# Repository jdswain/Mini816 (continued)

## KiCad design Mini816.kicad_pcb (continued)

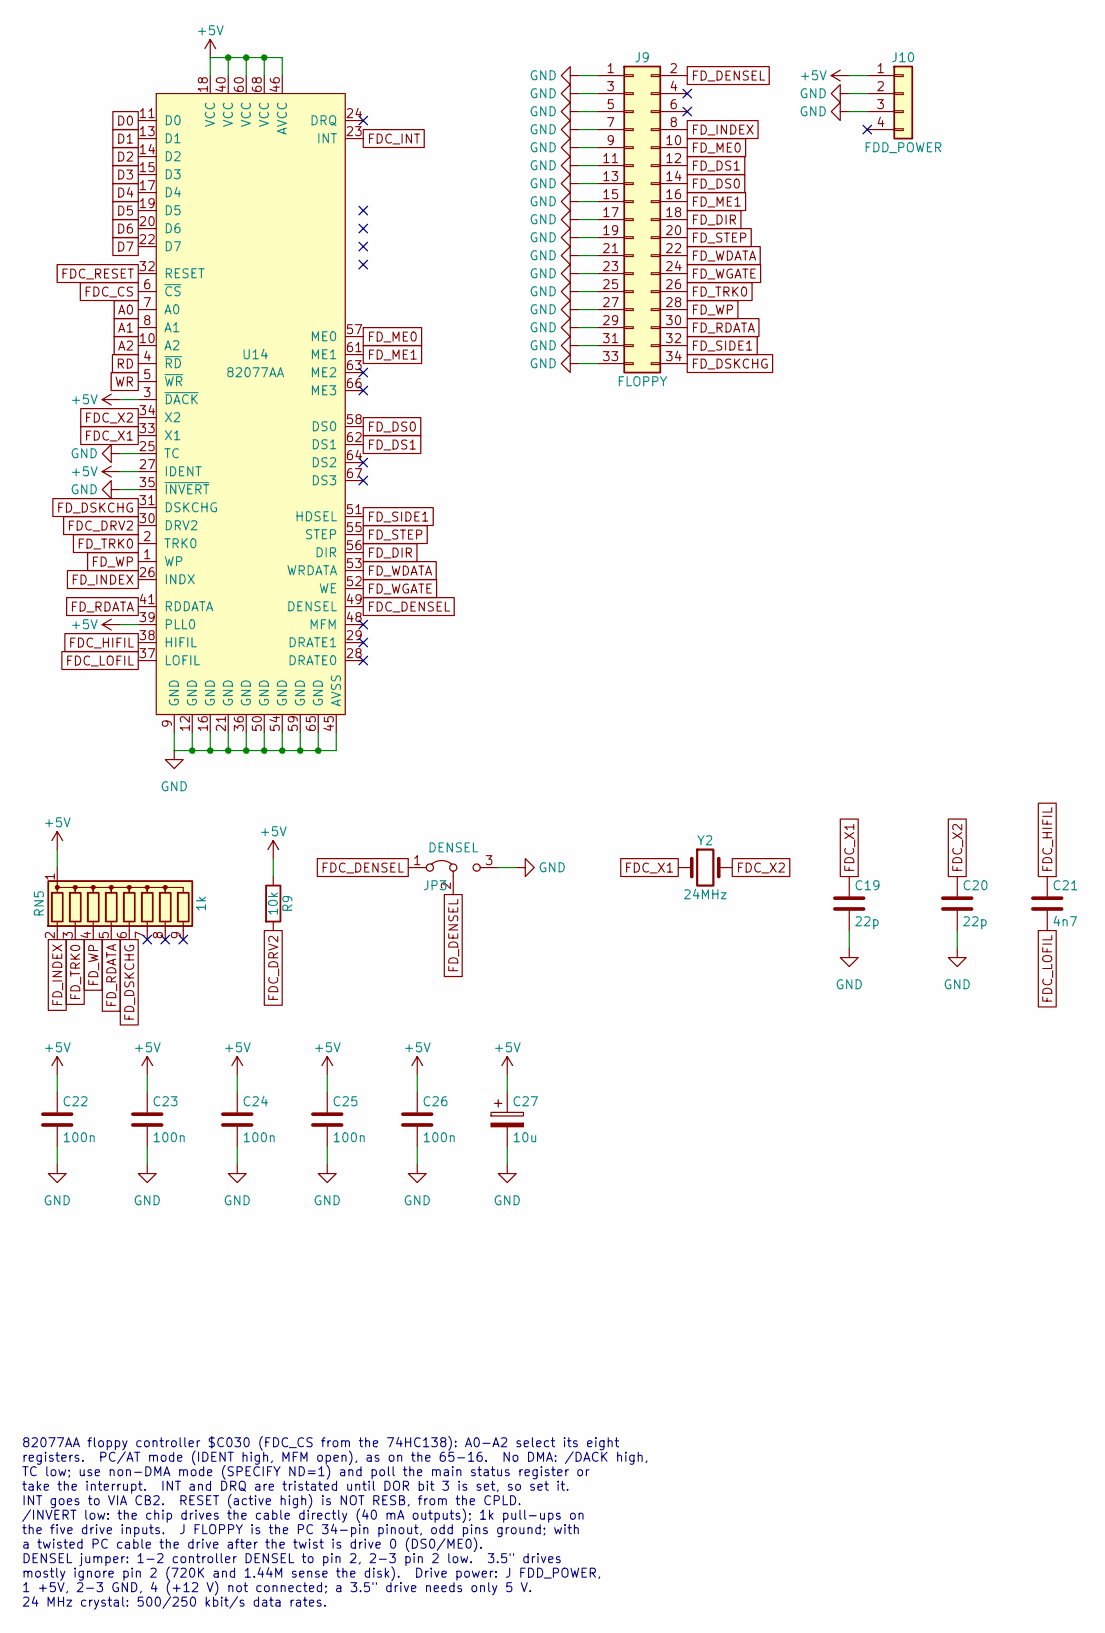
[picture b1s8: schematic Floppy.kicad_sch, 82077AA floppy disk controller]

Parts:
C19, C20: 22p; C_Disc_D5.0mm_W2.5mm_P5.00mm
C21: 4n7; C_Disc_D5.0mm_W2.5mm_P5.00mm
C22, C23, C24, C25, C26: 100n; C_Disc_D5.0mm_W2.5mm_P5.00mm
C27: 10u; CP_Radial_D6.3mm_P2.50mm
J9: FLOPPY; IDC-Header_2x17_P2.54mm_Vertical
J10: FDD_POWER; PinHeader_1x04_P2.54mm_Vertical
JP3: DENSEL; PinHeader_1x03_P2.54mm_Vertical
R9: 10k; R_Axial_DIN0207_L6.3mm_D2.5mm_P10.16mm_Horizontal
RN5: 1k; R_Array_SIP9
U14: 82077AA; PLCC-68_THT-Socket
Y2: 24MHz; Crystal_HC49-4H_Vertical

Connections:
+5V: C22.1, C23.1, C24.1, C25.1, C26.1, C27.1, J10.1, R9.1, RN5.1 (common), U14.3 (~DACK), U14.18 (VCC), U14.27 (IDENT), U14.39 (PLL0), U14.40 (VCC), U14.46 (AVCC), U14.60 (VCC), U14.68 (VCC); also elsewhere on the board
A0: U14.7 (A0); also elsewhere on the board
A1: U14.8 (A1); also elsewhere on the board
A2: U14.10 (A2); also elsewhere on the board
D0: U14.11 (D0); also elsewhere on the board
D1: U14.13 (D1); also elsewhere on the board
D2: U14.14 (D2); also elsewhere on the board
D3: U14.15 (D3); also elsewhere on the board
D4: U14.17 (D4); also elsewhere on the board
D5: U14.19 (D5); also elsewhere on the board
D6: U14.20 (D6); also elsewhere on the board
D7: U14.22 (D7); also elsewhere on the board
FDC_CS: U14.6 (~CS); also elsewhere on the board
FDC_DENSEL: JP3.1 (A), U14.49 (DENSEL)
FDC_DRV2: R9.2, U14.30 (DRV2)
FDC_HIFIL: C21.1, U14.38 (HIFIL)
FDC_INT: U14.23 (INT); also elsewhere on the board
FDC_LOFIL: C21.2, U14.37 (LOFIL)
FDC_RESET: U14.32 (RESET); also elsewhere on the board
FDC_X1: C19.1, U14.33 (X1), Y2.1
FDC_X2: C20.1, U14.34 (X2), Y2.2
FD_DENSEL: J9.2, JP3.2 (C)
FD_DIR: J9.18, U14.56 (DIR)
FD_DS0: J9.14, U14.58 (DS0)
FD_DS1: J9.12, U14.62 (DS1)
FD_DSKCHG: J9.34, RN5.6 (R5), U14.31 (DSKCHG)
FD_INDEX: J9.8, RN5.2 (R1), U14.26 (INDX)
FD_ME0: J9.10, U14.57 (ME0)
FD_ME1: J9.16, U14.61 (ME1)
FD_RDATA: J9.30, RN5.5 (R4), U14.41 (RDDATA)
FD_SIDE1: J9.32, U14.51 (HDSEL)
FD_STEP: J9.20, U14.55 (STEP)
FD_TRK0: J9.26, RN5.3 (R2), U14.2 (TRK0)
FD_WDATA: J9.22, U14.53 (WRDATA)
FD_WGATE: J9.24, U14.52 (WE)
FD_WP: J9.28, RN5.4 (R3), U14.1 (WP)
GND: C19.2, C20.2, C22.2, C23.2, C24.2, C25.2, C26.2, C27.2, J9.1, J9.3, J9.5, J9.7, J9.9, J9.11, J9.13, J9.15, J9.17, J9.19, J9.21, J9.23, J9.25, J9.27, J9.29, J9.31, J9.33, J10.2, J10.3, JP3.3 (B), U14.9 (GND), U14.12 (GND), U14.16 (GND), U14.21 (GND), U14.25 (TC), U14.35 (~INVERT), U14.36 (GND), U14.45 (AVSS), U14.50 (GND), U14.54 (GND), U14.59 (GND), U14.65 (GND); also elsewhere on the board
RD: U14.4 (~RD); also elsewhere on the board
WR: U14.5 (~WR); also elsewhere on the board

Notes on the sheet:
82077AA floppy controller $C030 (FDC_CS from the 74HC138): A0-A2 select its eight registers. PC/AT mode (IDENT high, MFM open), as on the 65-16. No DMA: /DACK high, TC low; use non-DMA mode (SPECIFY ND=1) and poll the main status register or take the interrupt. INT and DRQ are tristated until DOR b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

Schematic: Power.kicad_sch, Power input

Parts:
C28: 10u 25V; CP_Radial_D6.3mm_P2.50mm
C29: 22u 10V; CP_Radial_D6.3mm_P2.50mm
C30: 100u; CP_Radial_D6.3mm_P2.50mm
D2: 1N5819; D_DO-41_SOD81_P10.16mm_Horizontal
D3: POWER; LED_D3.0mm
F1: RXEF160; Fuse_Littelfuse_RXEF110; MPN Littelfuse RXEF160
H1, H2, H3, H4: M3; MountingHole_3.2mm_M3
J11: 12V_IN; BarrelJack_Horizontal
J12: LCD_12V; PinHeader_1x02_P2.54mm_Vertical
JP4: PWR_SRC; PinHeader_1x03_P2.54mm_Vertical
R10: 1k; R_Axial_DIN0207_L6.3mm_D2.5mm_P10.16mm_Horizontal
SW3: T8019L; SW_Salecom_T8019L; MPN Salecom T8019L
U15: R-78K5.0-2.0; Converter_DCDC_RECOM_R-78B-2.0_THT

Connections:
+5V: C30.1, F1.2, R10.1; also elsewhere on the board
+12V: C28.1, J12.1, SW3.3 (C), U15.1 (IN)
GND: C28.2, C29.2, C30.2, D3.1 (K), J11.2, J12.2, U15.2 (GND); also elsewhere on the board
PWR_LED: D3.2 (A), R10.2
REG_5V: C29.1, JP4.3 (B), U15.3 (OUT)
USB_5V: JP4.1 (A); also elsewhere on the board
V12_RAW: D2.1 (K), SW3.2 (B)
VIN12: D2.2 (A), J11.1
VSEL: F1.1, JP4.2 (C)

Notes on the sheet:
Normal power: a 12 V plug pack (centre positive) on the barrel jack. D is reverse- polarity protection; the T8019L toggle switches the 12 V. +12V goes to the 2-pin LCD_12V header for the composite LCD monitor, and to the Recom R-78K5.0-2.0 switching regulator (2 A, 6.5-36 V in), which makes REG_5V.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

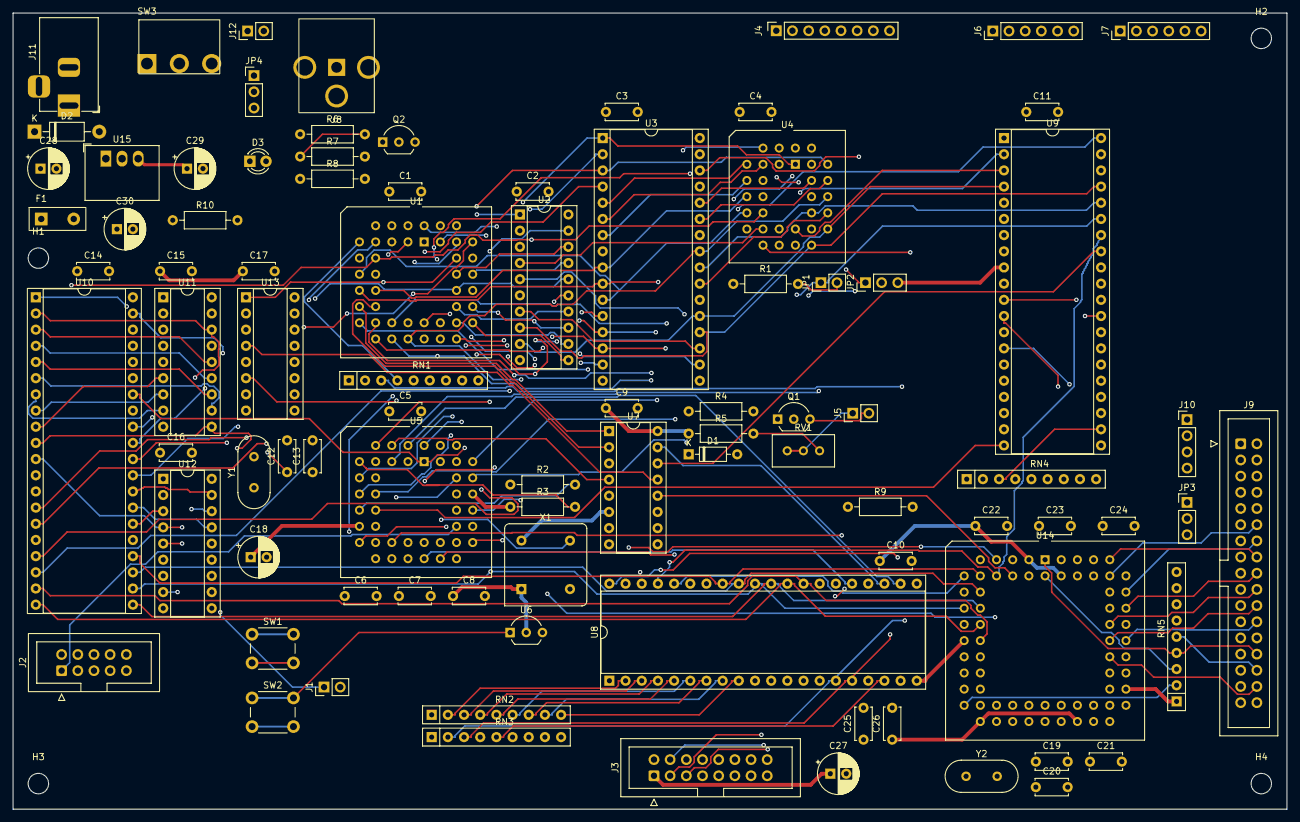
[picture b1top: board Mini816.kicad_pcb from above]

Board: 4 copper layers, 200.0 x 125.0 mm, 93 parts (0 on the bottom side), 159 nets.
